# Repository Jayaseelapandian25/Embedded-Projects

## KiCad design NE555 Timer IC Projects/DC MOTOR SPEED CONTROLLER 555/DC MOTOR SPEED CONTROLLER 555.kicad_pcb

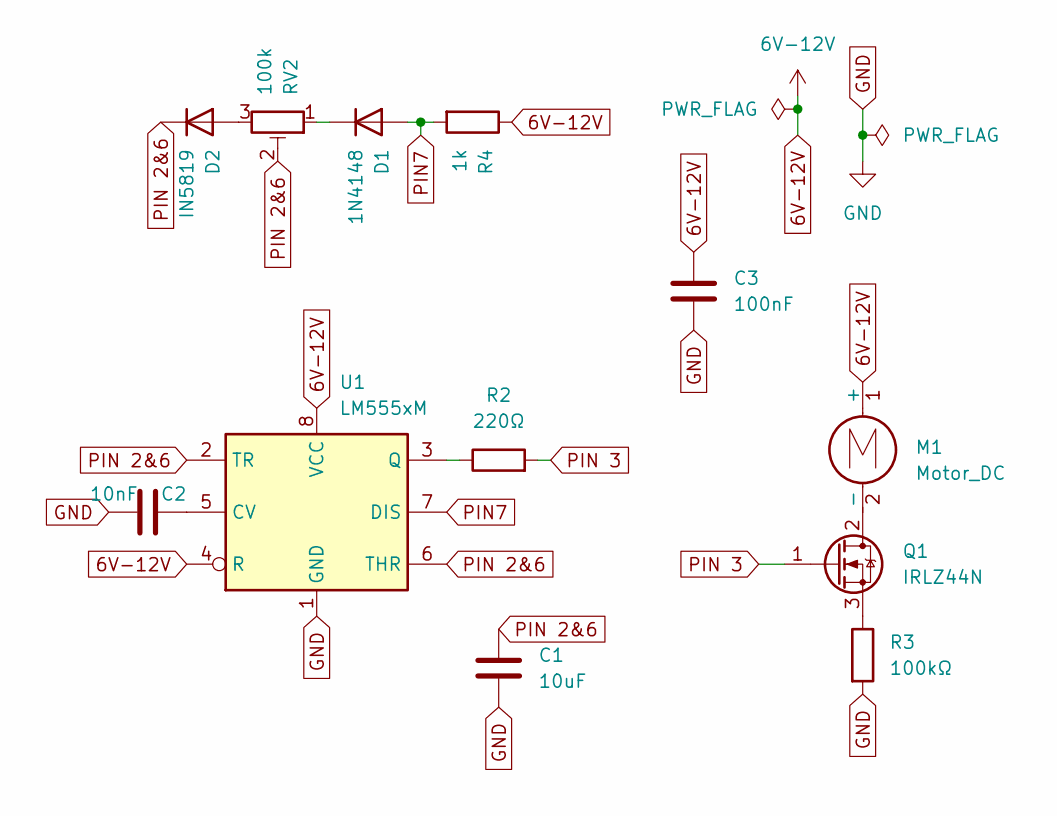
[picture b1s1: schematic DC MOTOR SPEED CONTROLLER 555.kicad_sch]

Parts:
C1: 10uF; C_0805_2012Metric_Pad1.18x1.45mm_HandSolder
C2: 10nF; C_0805_2012Metric_Pad1.18x1.45mm_HandSolder
C3: 100nF; C_0805_2012Metric_Pad1.18x1.45mm_HandSolder
D1: 1N4148; D_SOD-123
D2: IN5819; D_SOD-123
M1: Motor_DC; PinHeader_1x02_P2.54mm_Vertical
Q1: IRLZ44N; TO-220-3_Vertical
R2: 220Ω; R_0805_2012Metric_Pad1.20x1.40mm_HandSolder
R3: 100kΩ; R_0805_2012Metric_Pad1.20x1.40mm_HandSolder
R4: 1k; R_0805_2012Metric_Pad1.20x1.40mm_HandSolder
RV2: 100k; Potentiometer_Bourns_3296W_Vertical
U1: LM555xM; SOIC-8_3.9x4.9mm_P1.27mm

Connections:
6V-12V: C3.1, M1.1 (+), R4.1, U1.4 (R), U1.8 (VCC)
GND: C1.2, C2.1, C3.2, R3.2, U1.1 (GND)
unnamed: D1.1 (K), RV2.1
unnamed: D2.2 (A), RV2.3
unnamed: M1.2 (-), Q1.2 (D)
unnamed: Q1.3 (S), R3.1
unnamed: C2.2, U1.5 (CV)
unnamed: R2.1, U1.3 (Q)
PIN7: D1.2 (A), R4.2, U1.7 (DIS)
PIN 2&6: C1.1, D2.1 (K), RV2.2, U1.2 (TR), U1.6 (THR)
PIN 3: Q1.1 (G), R2.2

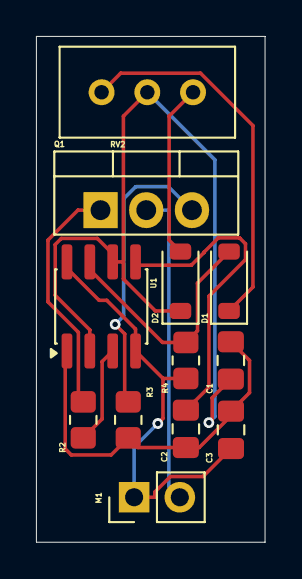
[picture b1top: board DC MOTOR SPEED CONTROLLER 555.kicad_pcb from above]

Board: 2 copper layers, 12.7 x 28.1 mm, 12 parts (0 on the bottom side), 11 nets.

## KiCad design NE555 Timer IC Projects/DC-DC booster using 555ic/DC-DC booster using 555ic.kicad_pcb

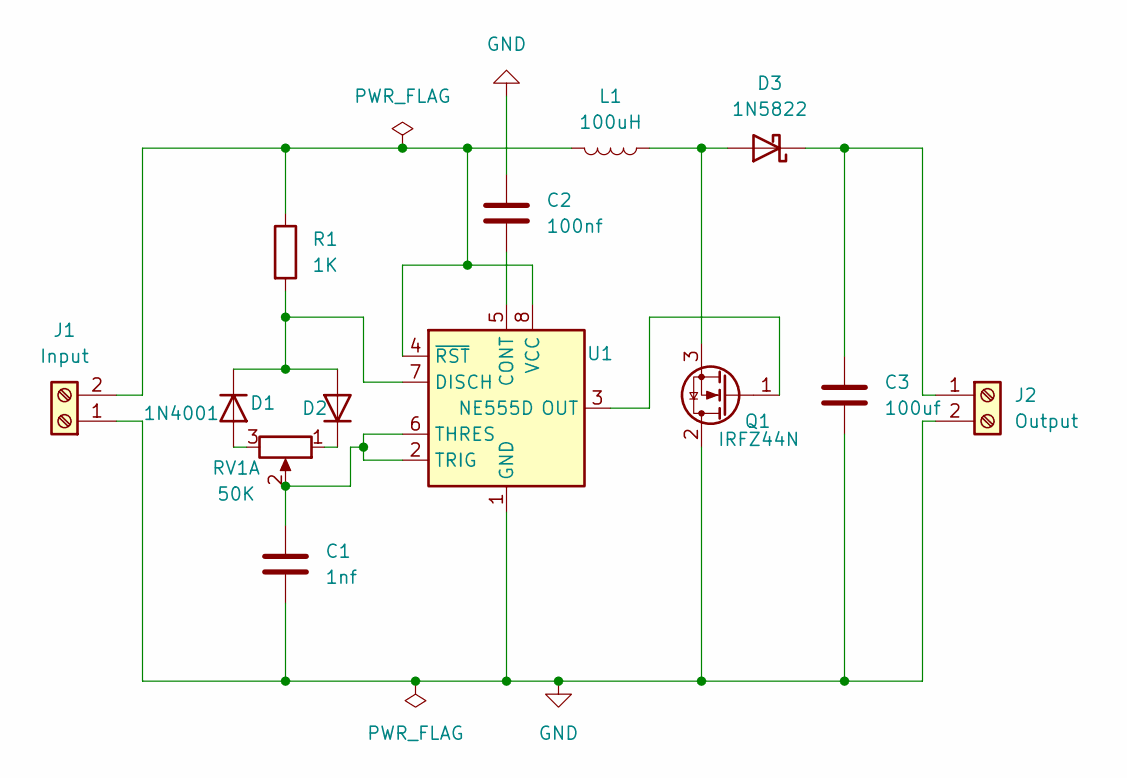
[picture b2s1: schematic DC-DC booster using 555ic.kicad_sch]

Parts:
C1: 1nf; CP_Radial_D6.3mm_P2.50mm
C2: 100nf; C_Disc_D5.0mm_W2.5mm_P5.00mm
C3: 100uf; CP_Radial_D6.3mm_P2.50mm
D1, D2: 1N4001; D_DO-41_SOD81_P10.16mm_Horizontal
D3: 1N5822; D_DO-201AD_P15.24mm_Horizontal
J1: Input; TerminalBlock_MaiXu_MX126-5.0-02P_1x02_P5.00mm
J2: Output; TerminalBlock_MaiXu_MX126-5.0-02P_1x02_P5.00mm
L1: 100uH; L_Radial_D10.0mm_P5.00mm_Fastron_07P
Q1: IRFZ44N; TO-220-3_Vertical
R1: 1K; R_Axial_DIN0207_L6.3mm_D2.5mm_P7.62mm_Horizontal
RV1: 50K; Potentiometer_Bourns_3296W_Vertical
U1: NE555D; SOIC-8_3.9x4.9mm_P1.27mm

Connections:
GND: C1.2, C2.2, C3.2, J1.1, J2.2, Q1.2 (D), U1.1 (GND)
unnamed: D1.2 (A), RV1.3
unnamed: D1.1 (K), D2.2 (A), R1.2, U1.7 (DISCH)
unnamed: D2.1 (K), RV1.1
unnamed: D3.2 (A), L1.1, Q1.3 (S)
unnamed: C3.1, D3.1 (K), J2.1
unnamed: J1.2, L1.2, R1.1, U1.4 (~RST), U1.8 (VCC)
unnamed: Q1.1 (G), U1.3 (OUT)
unnamed: C2.1, U1.5 (CONT)
unnamed: C1.1, RV1.2, U1.2 (TRIG), U1.6 (THRES)

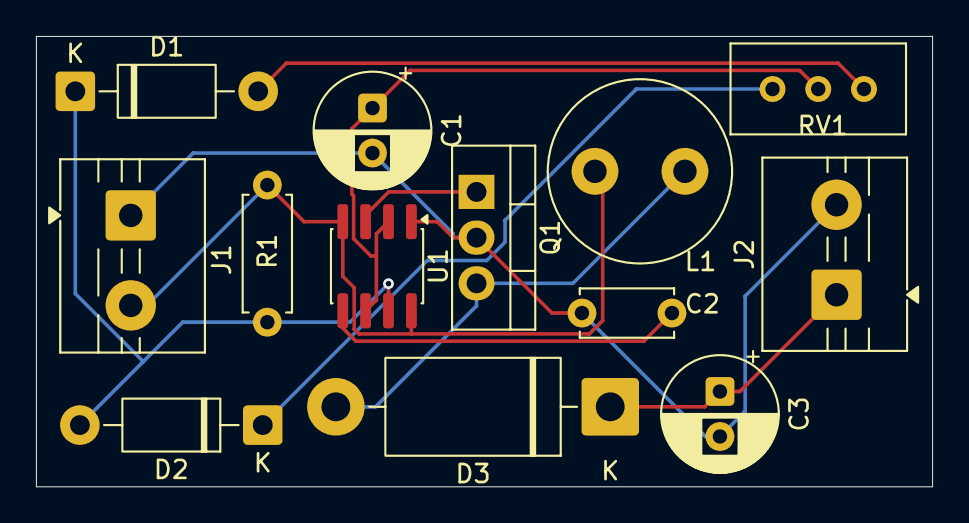
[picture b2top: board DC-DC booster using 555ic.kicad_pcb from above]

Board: 2 copper layers, 49.8 x 25.0 mm, 13 parts (0 on the bottom side), 10 nets.

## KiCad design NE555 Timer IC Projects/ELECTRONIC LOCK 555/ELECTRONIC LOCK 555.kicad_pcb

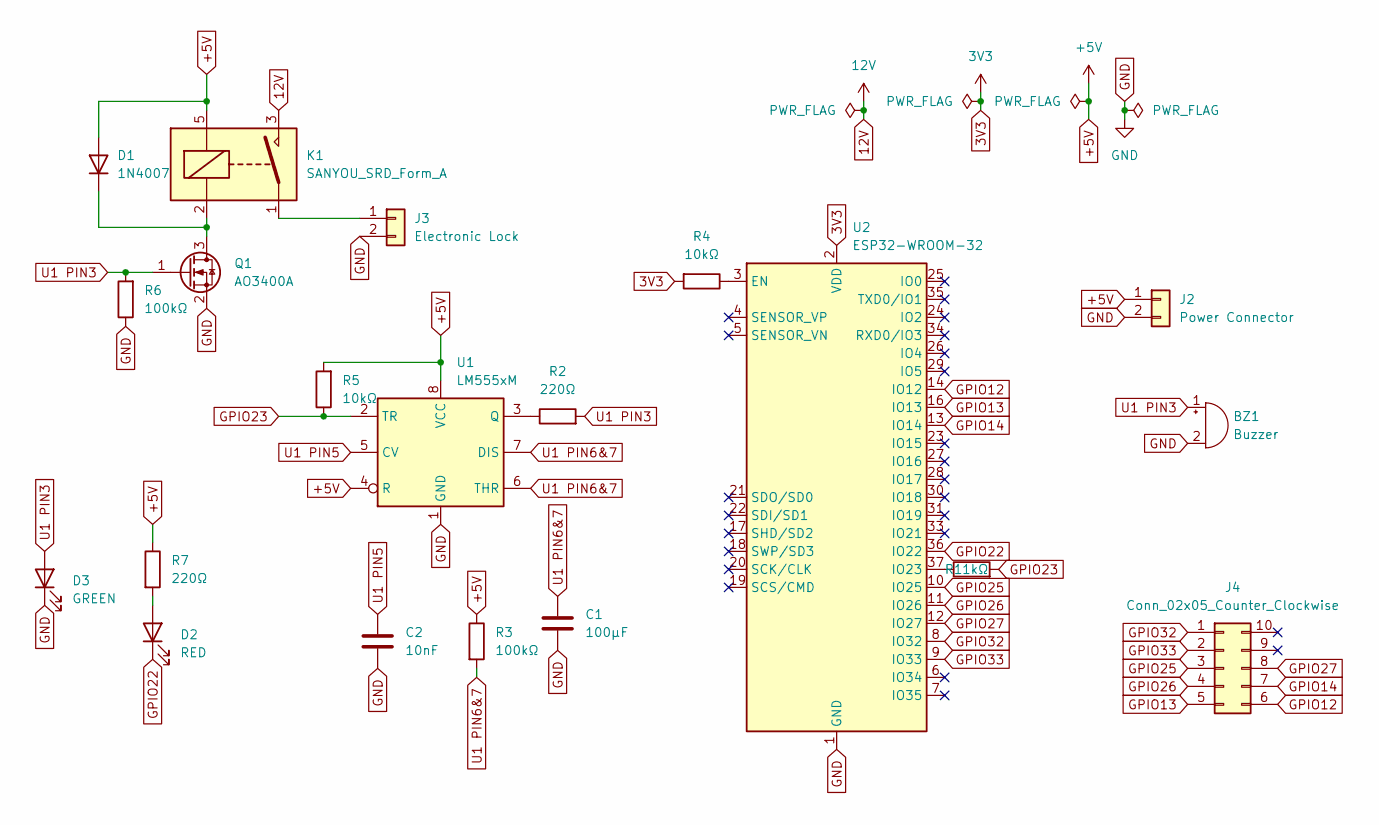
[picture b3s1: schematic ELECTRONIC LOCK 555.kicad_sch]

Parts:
BZ1: Buzzer; Buzzer_TDK_PS1240P02BT_D12.2mm_H6.5mm
C1: 100µF; C_0805_2012Metric
C2: 10nF; C_0805_2012Metric
D1: 1N4007; D_SMA
D2: RED; LED_0805_2012Metric
D3: GREEN; LED_0805_2012Metric
J2: Power Connector; JST_PH_B2B-PH-K_1x02_P2.00mm_Vertical
J3: Electronic Lock; JST_PH_B2B-PH-K_1x02_P2.00mm_Vertical
J4: Conn_02x05_Counter_Clockwise; IDC-Header_2x05_P2.54mm_Horizontal
K1: SANYOU_SRD_Form_A; Relay_SPST_SANYOU_SRD_Series_Form_A
Q1: AO3400A; SOT-23
R1: 1kΩ; R_0805_2012Metric
R2, R7: 220Ω; R_0805_2012Metric
R3, R6: 100kΩ; R_0805_2012Metric
R4, R5: 10kΩ; R_0805_2012Metric
U1: LM555xM; SOIC-8_3.9x4.9mm_P1.27mm
U2: ESP32-WROOM-32

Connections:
3V3: R4.2, U2.2 (VDD)
12V: K1.3
+5V: D1.2 (A), J2.1, K1.5, R3.1, R5.2, R7.1, U1.4 (R), U1.8 (VCC)
GND: BZ1.2 (-), C1.2, C2.2, D3.1 (K), J2.2, J3.2, Q1.2 (S), R6.1, U1.1 (GND), U2.1 (GND), U2.15 (GND), U2.38 (GND), U2.39 (GND)
GPIO12: J4.6, U2.14 (IO12)
GPIO13: J4.5, U2.16 (IO13)
GPIO14: J4.7, U2.13 (IO14)
GPIO22: D2.1 (K), U2.36 (IO22)
GPIO23: R1.2, R5.1, U1.2 (TR)
GPIO25: J4.3, U2.10 (IO25)
GPIO26: J4.4, U2.11 (IO26)
GPIO27: J4.8, U2.12 (IO27)
GPIO32: J4.1, U2.8 (IO32)
GPIO33: J4.2, U2.9 (IO33)
unnamed: D1.1 (K), K1.2, Q1.3 (D)
unnamed: D2.2 (A), R7.2
unnamed: J3.1, K1.1
unnamed: R2.1, U1.3 (Q)
unnamed: R4.1, U2.3 (EN)
unnamed: R1.1, U2.37 (IO23)
U1 PIN3: BZ1.1 (+), D3.2 (A), Q1.1 (G), R2.2, R6.2
U1 PIN5: C2.1, U1.5 (CV)
U1 PIN6&7: C1.1, R3.2, U1.6 (THR), U1.7 (DIS)

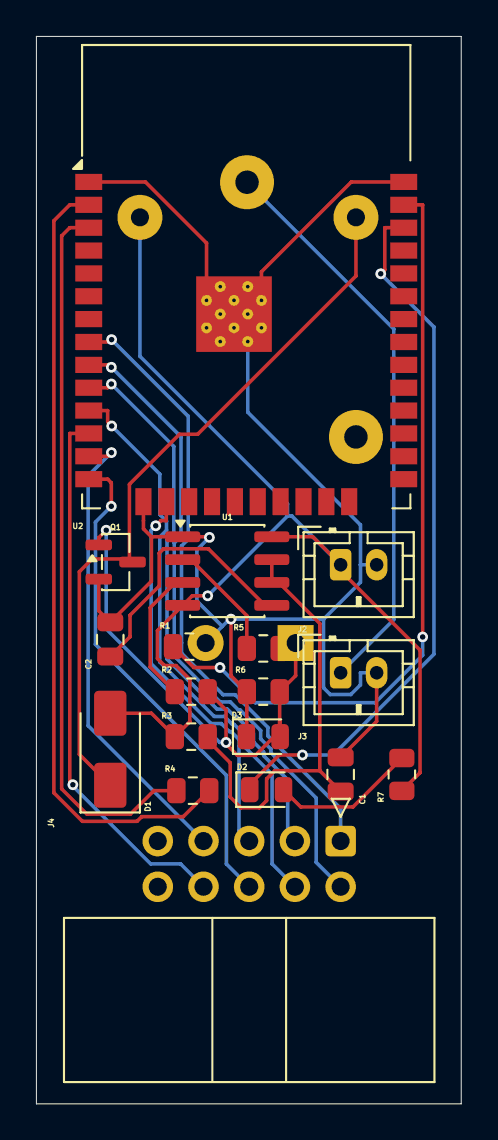
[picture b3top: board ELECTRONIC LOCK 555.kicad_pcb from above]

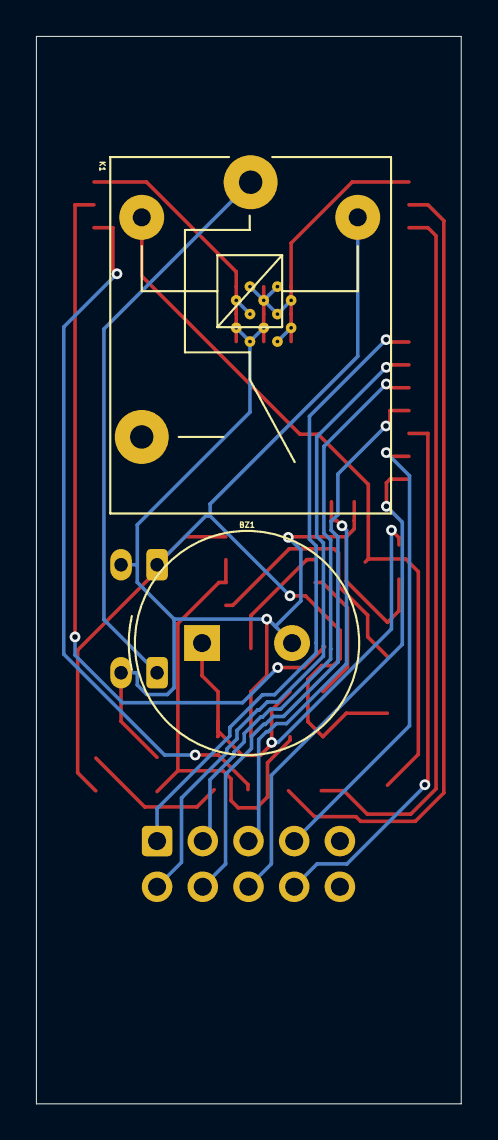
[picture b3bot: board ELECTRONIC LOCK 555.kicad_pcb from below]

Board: 2 copper layers, 23.6 x 59.3 mm, 20 parts (2 on the bottom side), 22 nets.

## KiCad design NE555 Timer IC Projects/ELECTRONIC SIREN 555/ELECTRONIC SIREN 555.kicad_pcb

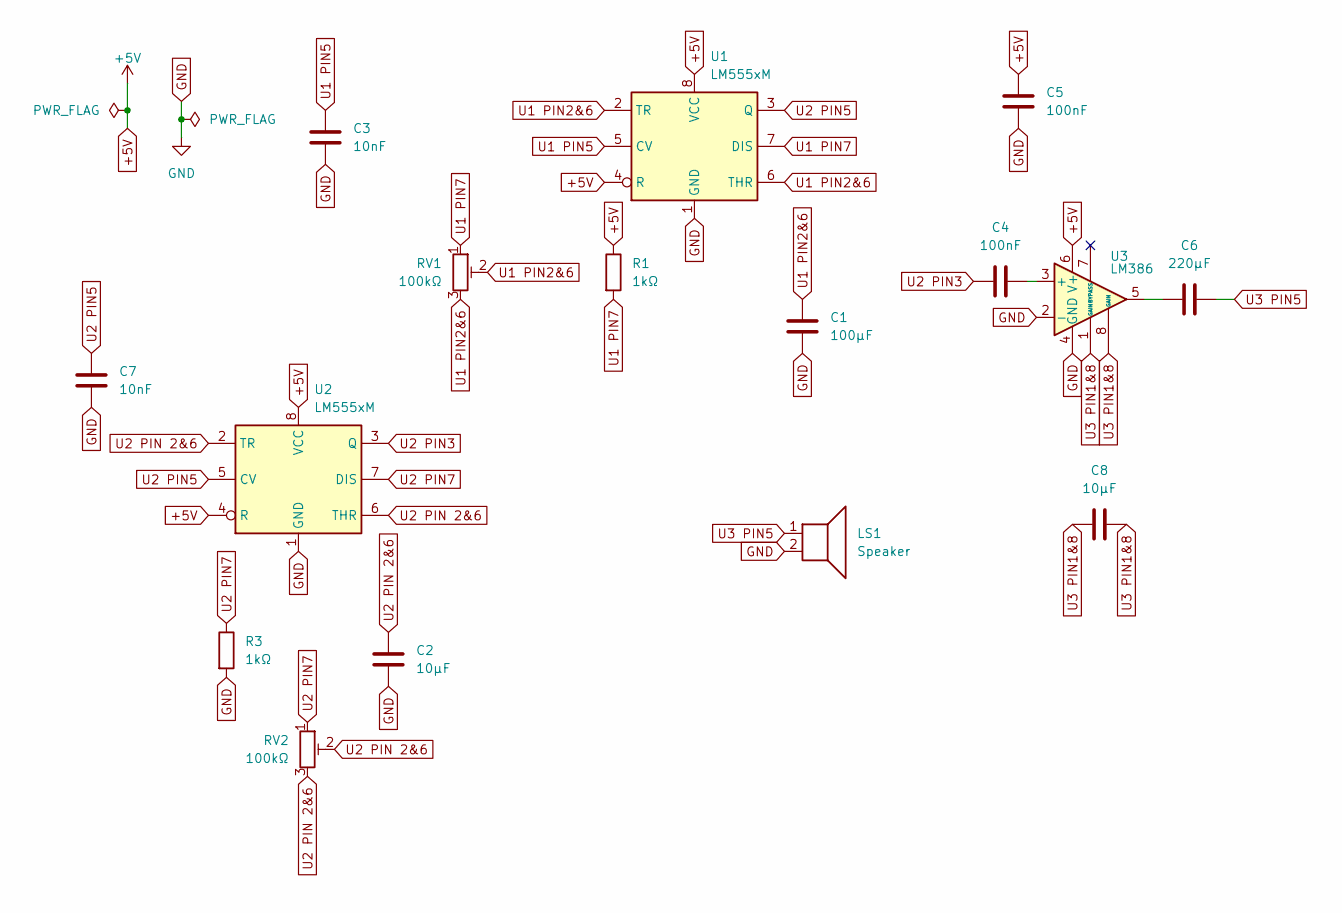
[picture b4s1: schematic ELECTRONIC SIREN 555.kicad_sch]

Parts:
C1: 100µF; C_0805_2012Metric
C2, C8: 10µF; C_0805_2012Metric
C3, C7: 10nF; C_0805_2012Metric
C4, C5: 100nF; C_0805_2012Metric
C6: 220µF; CP_Elec_6.3x5.4
LS1: Speaker; JST_PH_B2B-PH-K_1x02_P2.00mm_Vertical
R1, R3: 1kΩ; R_0805_2012Metric
RV1, RV2: 100kΩ; Potentiometer_Bourns_3296W_Vertical
U1, U2: LM555xM; SOIC-8_3.9x4.9mm_P1.27mm
U3: LM386; SOIC-8_3.9x4.9mm_P1.27mm

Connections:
+5V: C5.1, R1.1, U1.4 (R), U1.8 (VCC), U2.4 (R), U2.8 (VCC), U3.6 (V+)
GND: C1.2, C2.2, C3.2, C5.2, C7.2, LS1.2, R3.2, U1.1 (GND), U2.1 (GND), U3.2 (-), U3.4 (GND)
unnamed: C6.1, U3.5
unnamed: C4.2, U3.3 (+)
U1 PIN2&6: C1.1, RV1.2, RV1.3, U1.2 (TR), U1.6 (THR)
U1 PIN5: C3.1, U1.5 (CV)
U1 PIN7: R1.2, RV1.1, U1.7 (DIS)
U2 PIN3: C4.1, U2.3 (Q)
U2 PIN5: C7.1, U1.3 (Q), U2.5 (CV)
U2 PIN7: R3.1, RV2.1, U2.7 (DIS)
U2 PIN 2&6: C2.1, RV2.2, RV2.3, U2.2 (TR), U2.6 (THR)
U3 PIN1&8: C8.1, C8.2, U3.1 (GAIN), U3.8 (GAIN)
U3 PIN5: C6.2, LS1.1

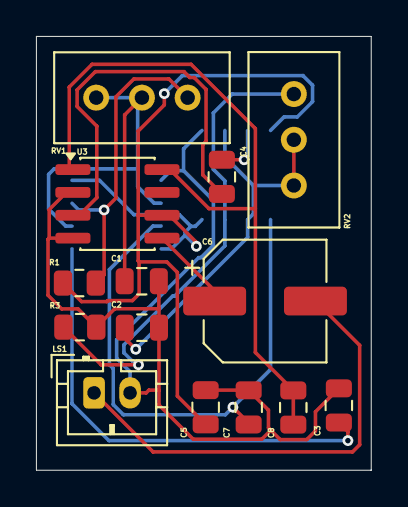
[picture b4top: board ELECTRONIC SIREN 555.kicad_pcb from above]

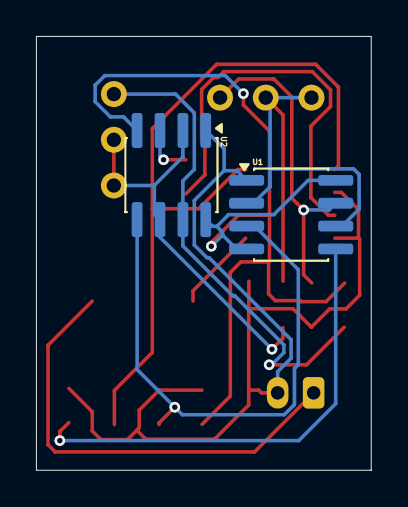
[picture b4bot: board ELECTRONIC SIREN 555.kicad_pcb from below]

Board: 2 copper layers, 18.6 x 24.1 mm, 16 parts (2 on the bottom side), 13 nets.

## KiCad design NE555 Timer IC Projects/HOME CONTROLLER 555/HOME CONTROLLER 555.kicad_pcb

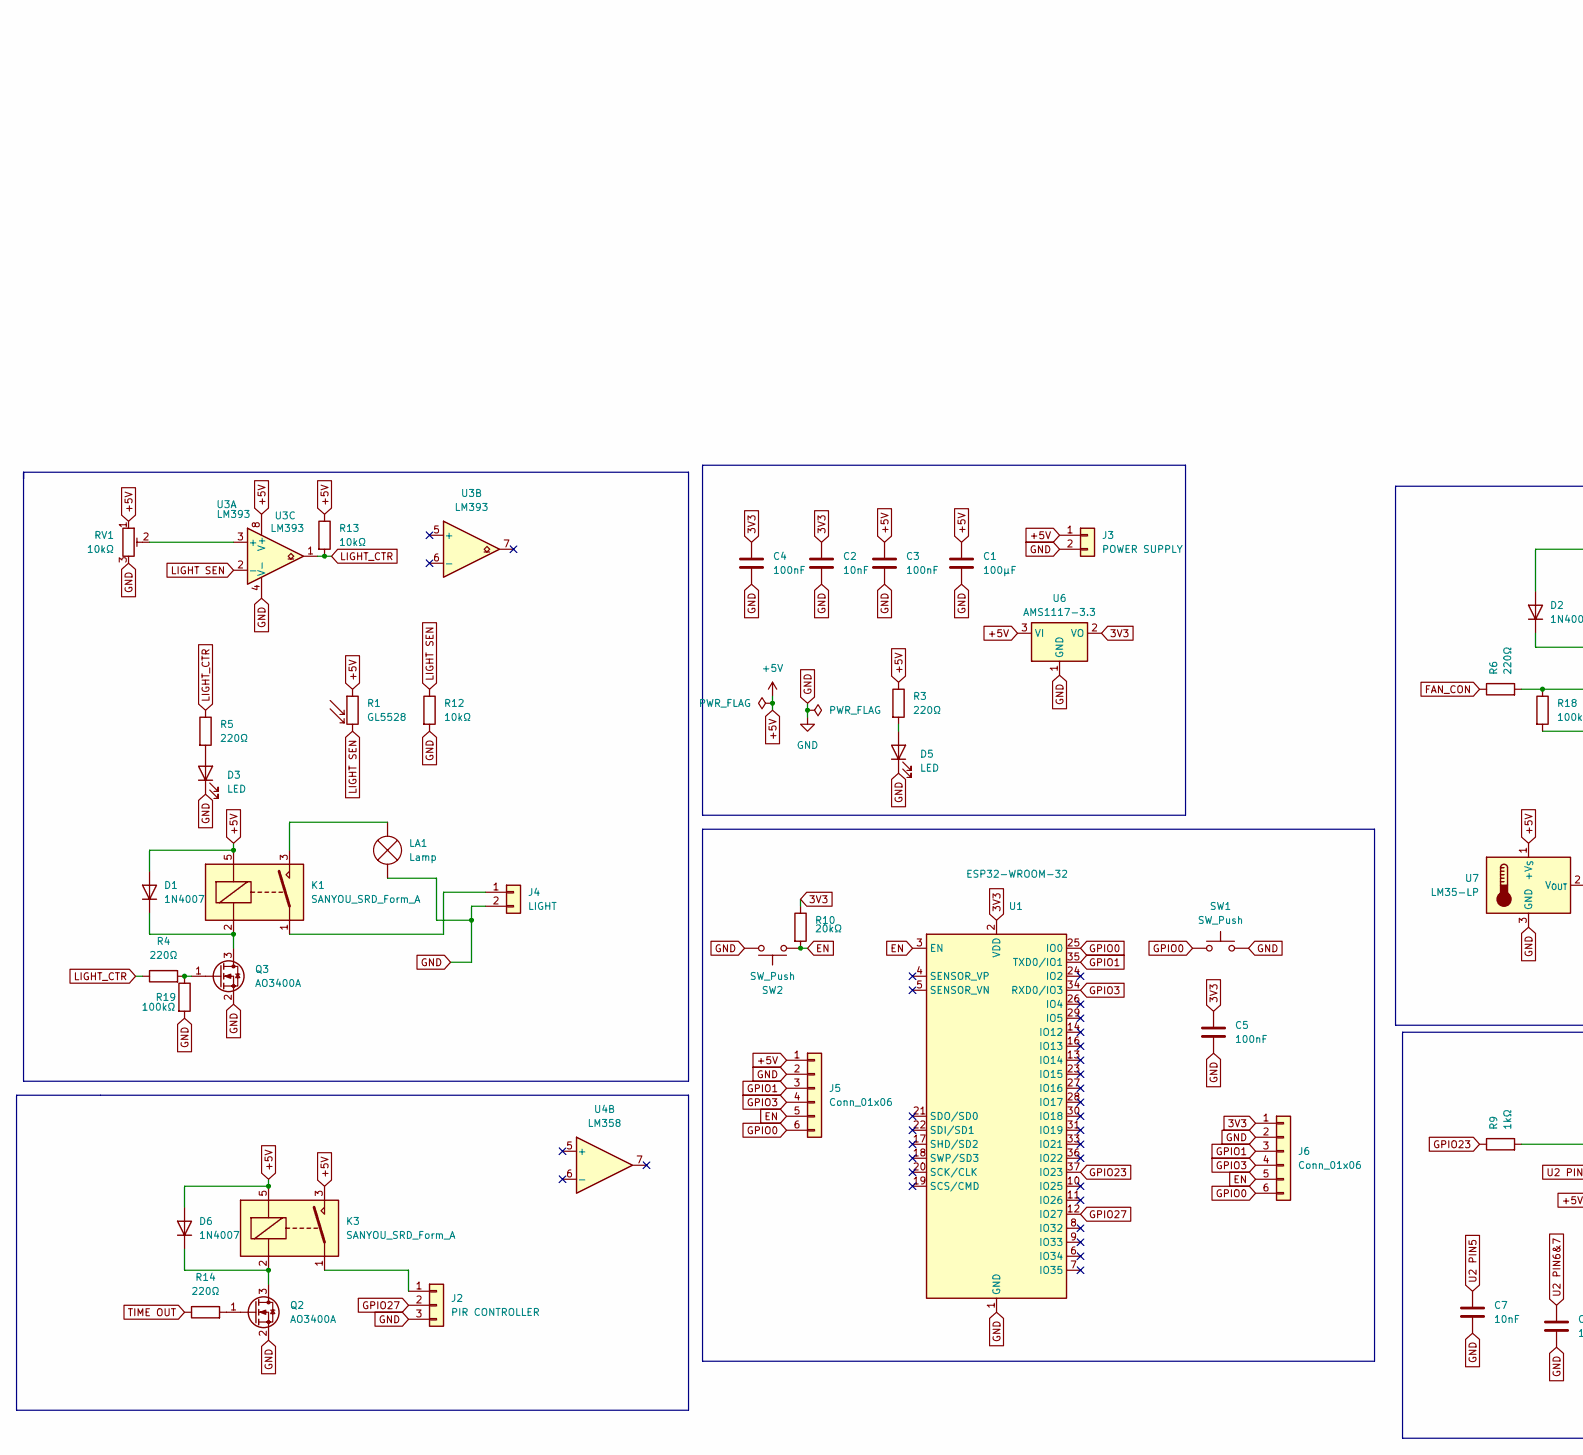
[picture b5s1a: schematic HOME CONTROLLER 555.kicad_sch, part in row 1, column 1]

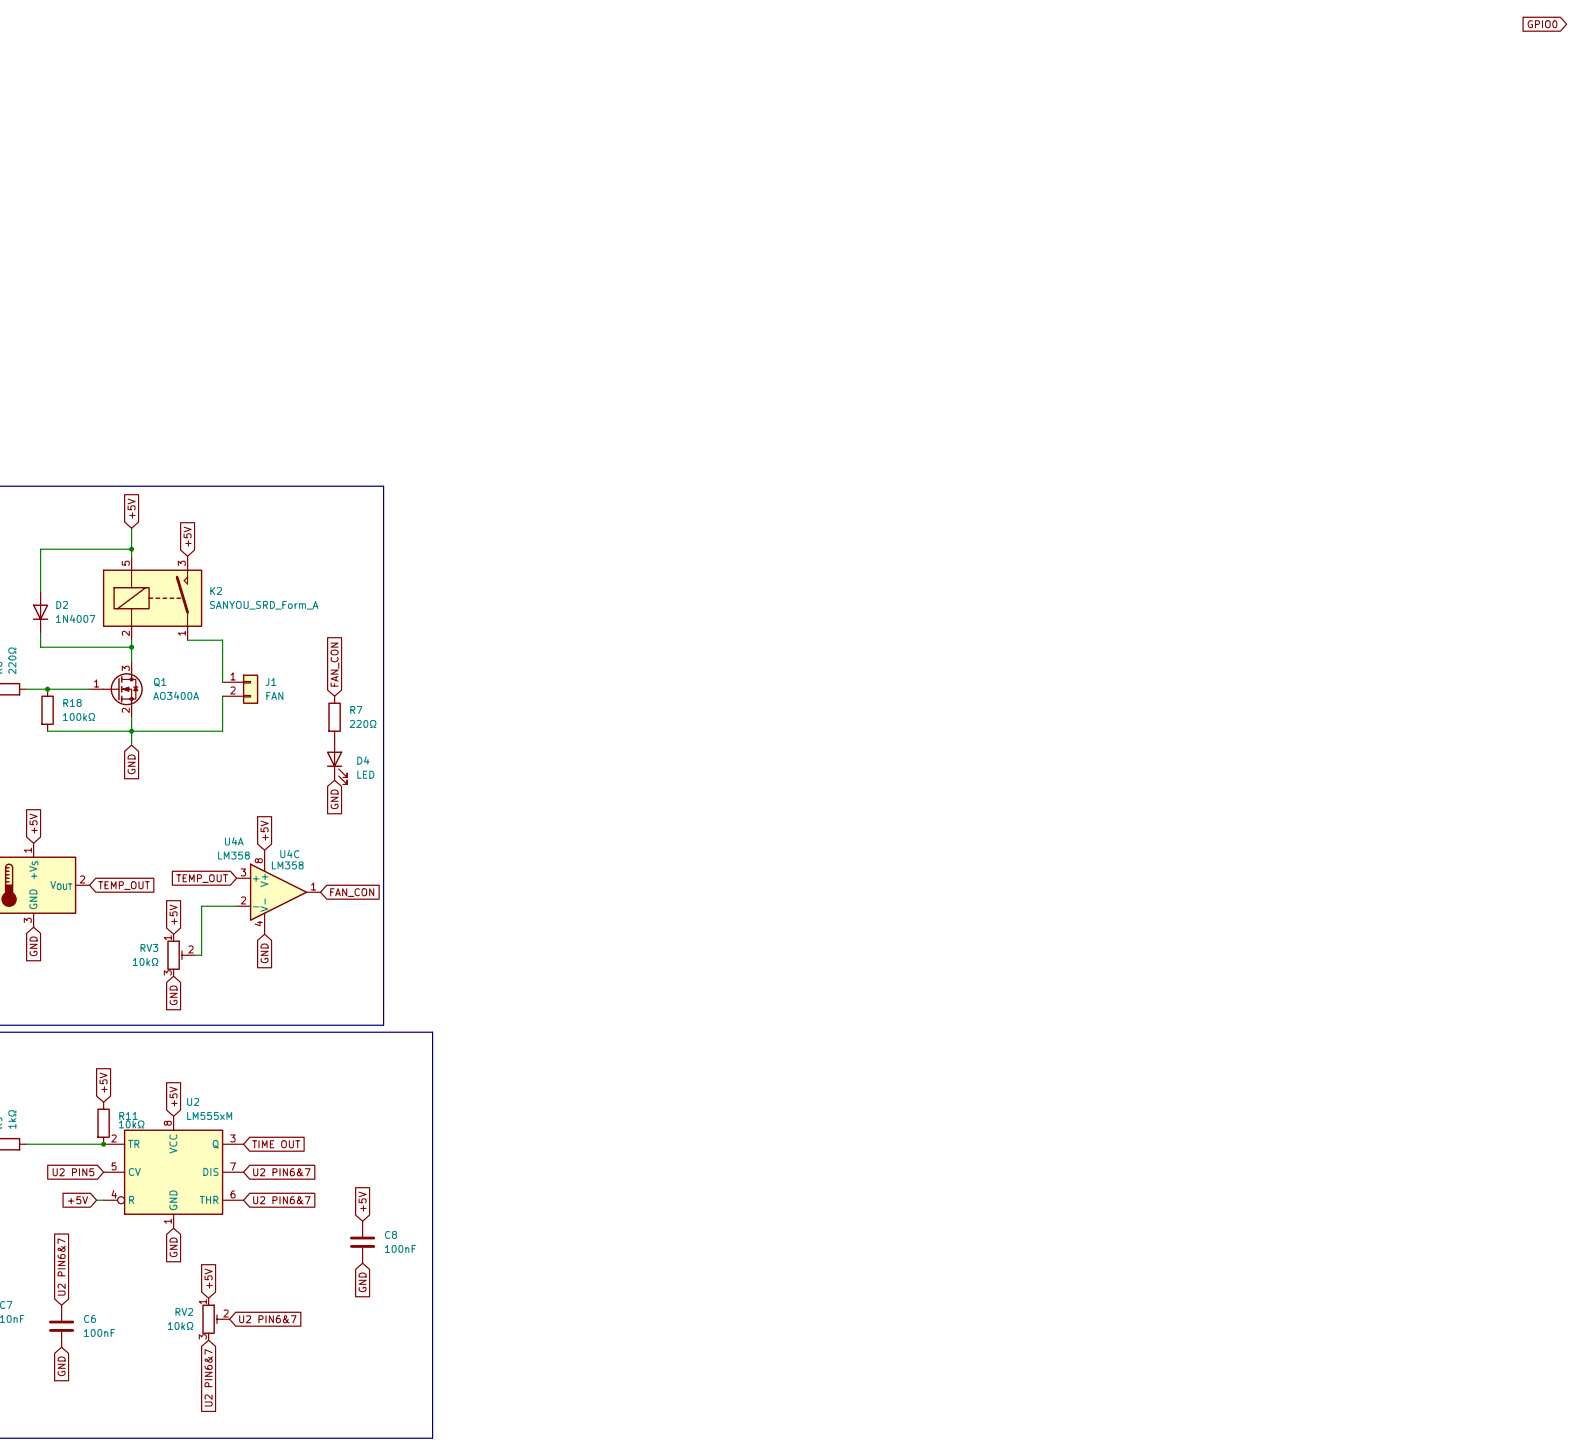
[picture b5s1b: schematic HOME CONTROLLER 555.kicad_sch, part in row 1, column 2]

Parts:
C1: 100µF; C_0805_2012Metric
C2, C7: 10nF; C_0805_2012Metric
C3, C4, C5, C6, C8: 100nF; C_0805_2012Metric
D1, D2, D6: 1N4007; D_SMA
D3, D4, D5: LED; LED_0805_2012Metric
J1: FAN; JST_PH_B2B-PH-K_1x02_P2.00mm_Vertical
J2: PIR CONTROLLER; PinHeader_1x03_P2.54mm_Vertical
J3: POWER SUPPLY; JST_PH_B2B-PH-K_1x02_P2.00mm_Vertical
J4: LIGHT; JST_PH_B2B-PH-K_1x02_P2.00mm_Vertical
J5, J6: Conn_01x06; PinHeader_1x06_P2.54mm_Vertical
K1, K2, K3: SANYOU_SRD_Form_A; Relay_SPST_SANYOU_SRD_Series_Form_A
LA1: Lamp; JST_PH_B2B-PH-K_1x02_P2.00mm_Vertical
Q1, Q2, Q3: AO3400A; SOT-23
R1: GL5528; R_LDR_5.1x4.3mm_P3.4mm_Vertical
R3, R4, R5, R6, R7, R14: 220Ω; R_0805_2012Metric
R9: 1kΩ; R_0805_2012Metric
R10: 20kΩ; R_0805_2012Metric
R11, R12, R13: 10kΩ; R_0805_2012Metric
R18, R19: 100kΩ; R_0805_2012Metric
RV1, RV2, RV3: 10kΩ; Potentiometer_Bourns_3296W_Vertical
SW1, SW2: SW_Push; SW_SPST_TL3342
U1: ESP32-WROOM-32
U2: LM555xM; SOIC-8_3.9x4.9mm_P1.27mm
U3: LM393; SOIC-8_3.9x4.9mm_P1.27mm
U4: LM358; SOIC-8_3.9x4.9mm_P1.27mm
U6: AMS1117-3.3; SOT-223-3_TabPin2
U7: LM35-LP; TO-92_Inline

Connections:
3V3: C2.1, C4.1, C5.1, J6.1, R10.1, U1.2 (VDD), U6.2 (VO)
+5V: C1.1, C3.1, C8.1, D1.2 (A), D2.2 (A), D6.2 (A), J3.1, J5.1, K1.5, K2.3, K2.5, K3.3, K3.5, R1.1, R3.1, R11.1, R13.1, RV1.1, RV2.1, RV3.1, U2.4 (R), U2.8 (VCC), U3.8 (V+), U4.8 (V+), U6.3 (VI), U7.1 (+V_{S})
EN: J5.5, J6.5, R10.2, SW2.1, U1.3 (EN)
FAN_CON: R6.1, R7.1, U4.1
GND: C1.2, C2.2, C3.2, C4.2, C5.2, C6.2, C7.2, C8.2, D3.1 (K), D4.1 (K), D5.1 (K), J1.2, J2.3, J3.2, J4.2, J5.2, J6.2, LA1.1 (-), Q1.2 (S), Q2.2 (S), Q3.2 (S), R12.2, R18.2, R19.2, RV1.3, RV3.3, SW1.2, SW2.2, U1.1 (GND), U1.15 (GND), U1.38 (GND), U1.39 (GND), U2.1 (GND), U3.4 (V-), U4.4 (V-), U6.1 (GND), U7.3 (GND)
GPIO0: J5.6, J6.6, SW1.1, U1.25 (IO0)
GPIO1: J5.3, J6.3, U1.35 (TXD0/IO1)
GPIO3: J5.4, J6.4, U1.34 (RXD0/IO3)
GPIO23: R9.1, U1.37 (IO23)
GPIO27: J2.2, U1.12 (IO27)
LIGHT SEN: R1.2, R12.1, U3.2 (-)
LIGHT_CTR: R4.1, R5.1, R13.2, U3.1
unnamed: D1.1 (K), K1.2, Q3.3 (D)
unnamed: D2.1 (K), K2.2, Q1.3 (D)
unnamed: D3.2 (A), R5.2
unnamed: D4.2 (A), R7.2
unnamed: D5.2 (A), R3.2
unnamed: D6.1 (K), K3.2, Q2.3 (D)
unnamed: J1.1, K2.1
unnamed: J2.1, K3.1
unnamed: J4.1, K1.1
unnamed: K1.3, LA1.2 (+)
unnamed: Q1.1 (G), R6.2, R18.1
unnamed: Q2.1 (G), R14.2
unnamed: Q3.1 (G), R4.2, R19.1
unnamed: R9.2, R11.2, U2.2 (TR)
unnamed: RV1.2, U3.3 (+)
unnamed: RV3.2, U4.2 (-)
TEMP_OUT: U4.3 (+), U7.2 (V_{OUT})
TIME OUT: R14.1, U2.3 (Q)
U2 PIN5: C7.1, U2.5 (CV)
U2 PIN6&7: C6.1, RV2.2, RV2.3, U2.6 (THR), U2.7 (DIS)

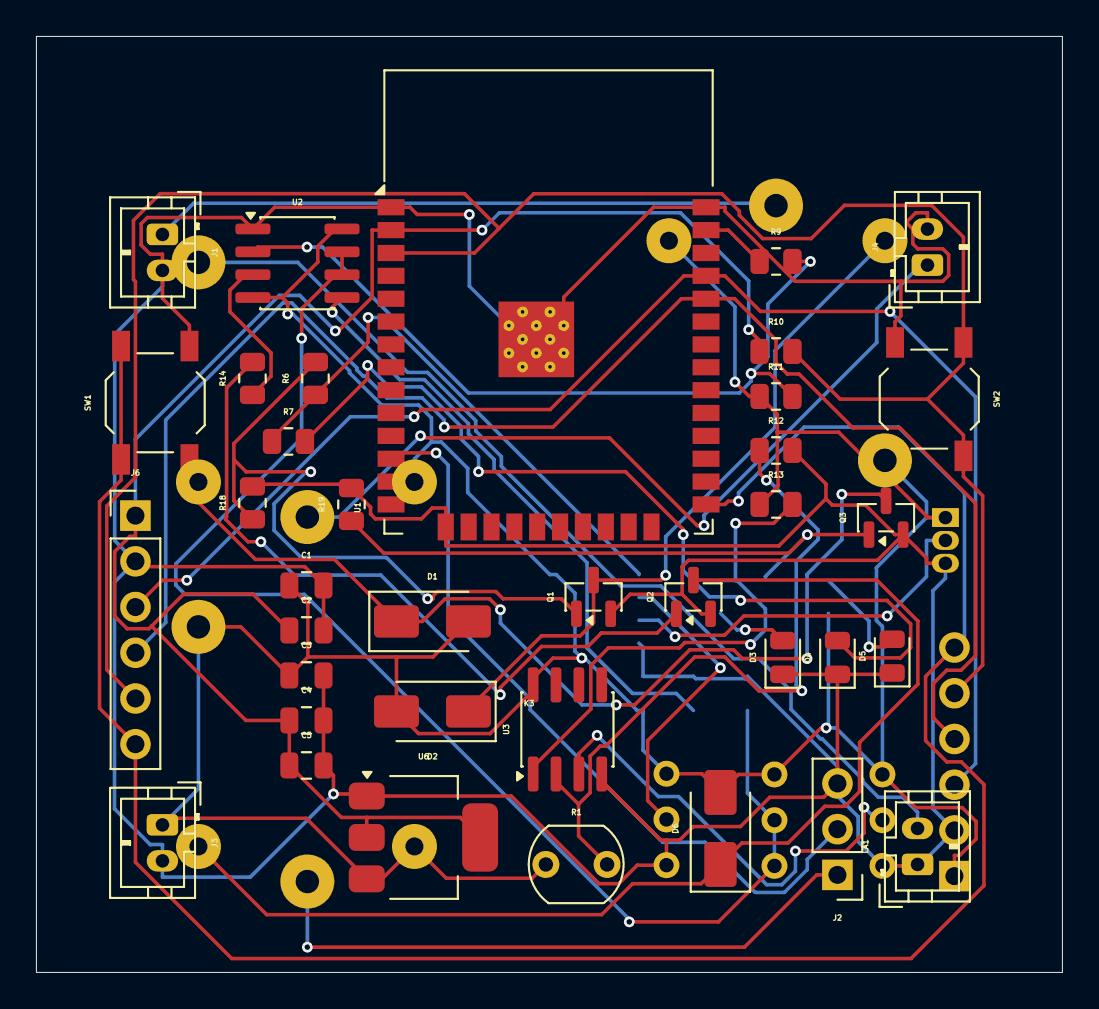
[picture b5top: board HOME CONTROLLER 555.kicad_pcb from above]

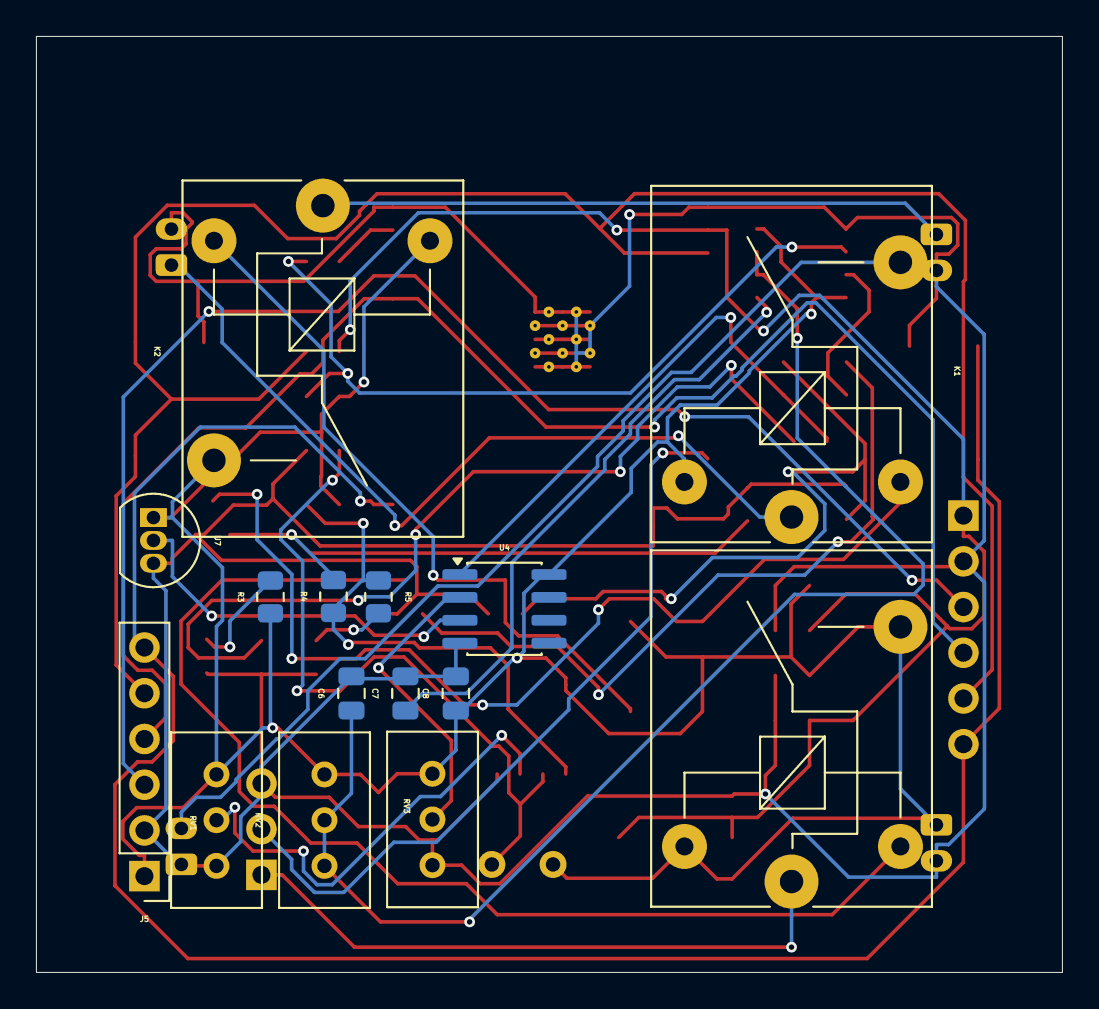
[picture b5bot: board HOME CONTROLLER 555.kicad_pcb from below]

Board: 2 copper layers, 57.0 x 52.0 mm, 52 parts (15 on the bottom side), 32 nets.

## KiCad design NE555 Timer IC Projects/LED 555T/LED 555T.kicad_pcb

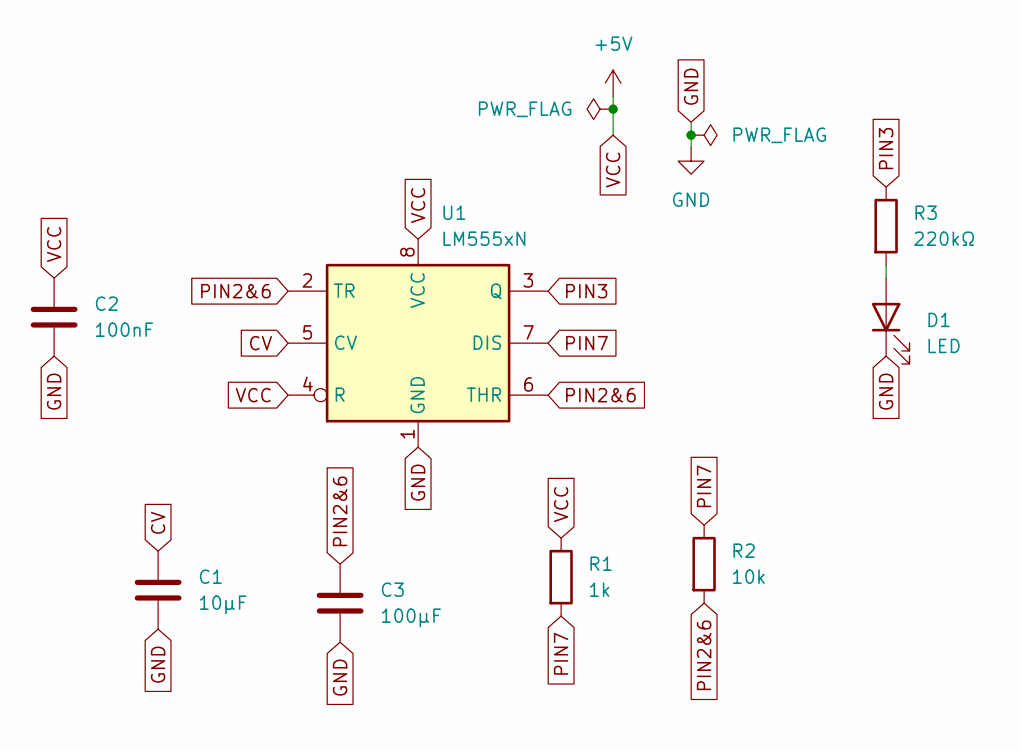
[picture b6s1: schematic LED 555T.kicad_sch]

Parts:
C1: 10µF; C_0805_2012Metric_Pad1.18x1.45mm_HandSolder
C2: 100nF; C_0805_2012Metric_Pad1.18x1.45mm_HandSolder
C3: 100µF; C_0805_2012Metric_Pad1.18x1.45mm_HandSolder
D1: LED; LED_0805_2012Metric
R1: 1k; R_0805_2012Metric_Pad1.20x1.40mm_HandSolder
R2: 10k; R_0805_2012Metric_Pad1.20x1.40mm_HandSolder
R3: 220kΩ; R_0805_2012Metric_Pad1.20x1.40mm_HandSolder
U1: LM555xN; DIP-8_W7.62mm

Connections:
CV: C1.1, U1.5 (CV)
GND: C1.2, C2.2, C3.2, D1.1 (K), U1.1 (GND)
unnamed: D1.2 (A), R3.2
PIN2&6: C3.1, R2.2, U1.2 (TR), U1.6 (THR)
PIN3: R3.1, U1.3 (Q)
PIN7: R1.2, R2.1, U1.7 (DIS)
VCC: C2.1, R1.1, U1.4 (R), U1.8 (VCC)

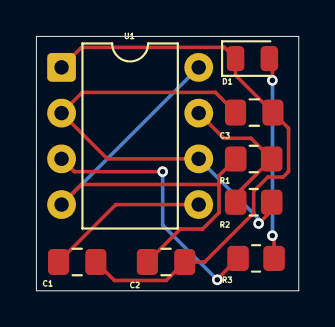
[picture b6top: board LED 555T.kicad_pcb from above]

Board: 2 copper layers, 14.6 x 14.1 mm, 8 parts (0 on the bottom side), 7 nets.

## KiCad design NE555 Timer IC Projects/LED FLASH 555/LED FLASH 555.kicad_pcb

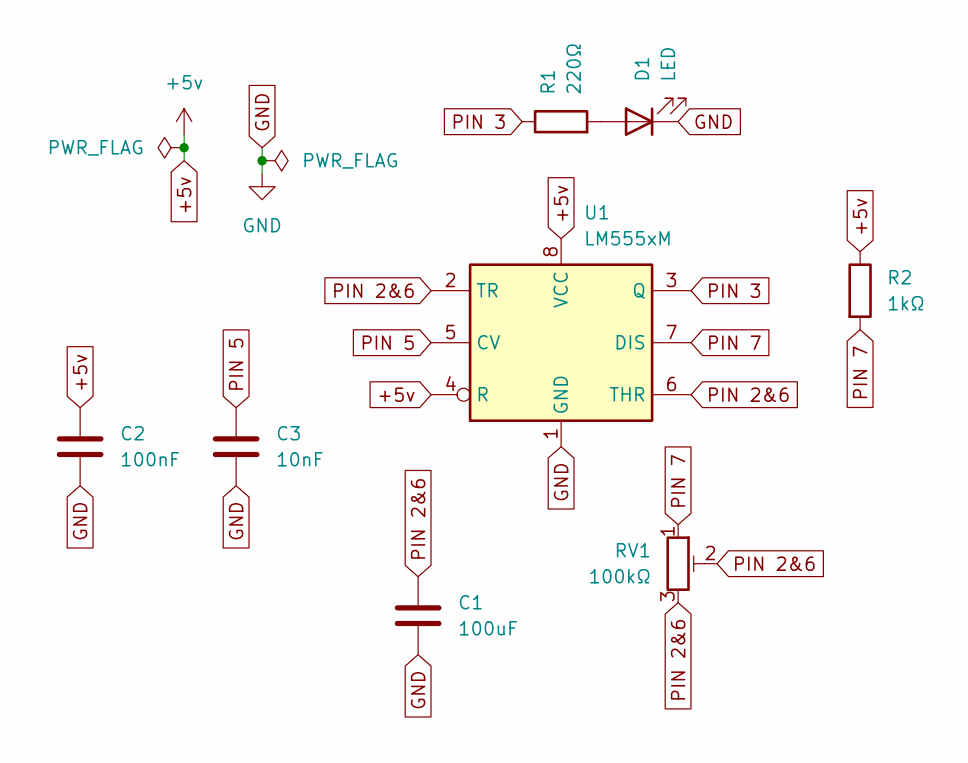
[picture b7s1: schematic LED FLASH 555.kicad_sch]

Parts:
C1: 100uF; C_0805_2012Metric_Pad1.18x1.45mm_HandSolder
C2: 100nF; C_0805_2012Metric_Pad1.18x1.45mm_HandSolder
C3: 10nF; C_0805_2012Metric_Pad1.18x1.45mm_HandSolder
D1: LED; LED_0805_2012Metric_Pad1.15x1.40mm_HandSolder
R1: 220Ω; R_0805_2012Metric_Pad1.20x1.40mm_HandSolder
R2: 1kΩ; R_0805_2012Metric_Pad1.20x1.40mm_HandSolder
RV1: 100kΩ; Potentiometer_Bourns_3296W_Vertical
U1: LM555xM; SOIC-8_3.9x4.9mm_P1.27mm

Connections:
+5v: C2.1, R2.1, U1.4 (R), U1.8 (VCC)
GND: C1.2, C2.2, C3.2, D1.1 (K), U1.1 (GND)
unnamed: D1.2 (A), R1.2
PIN 2&6: C1.1, RV1.2, RV1.3, U1.2 (TR), U1.6 (THR)
PIN 3: R1.1, U1.3 (Q)
PIN 5: C3.1, U1.5 (CV)
PIN 7: R2.2, RV1.1, U1.7 (DIS)

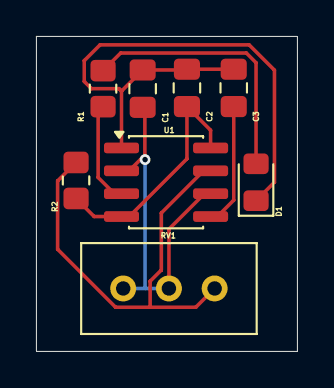
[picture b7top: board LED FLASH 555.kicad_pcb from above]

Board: 2 copper layers, 14.5 x 17.5 mm, 8 parts (0 on the bottom side), 7 nets.

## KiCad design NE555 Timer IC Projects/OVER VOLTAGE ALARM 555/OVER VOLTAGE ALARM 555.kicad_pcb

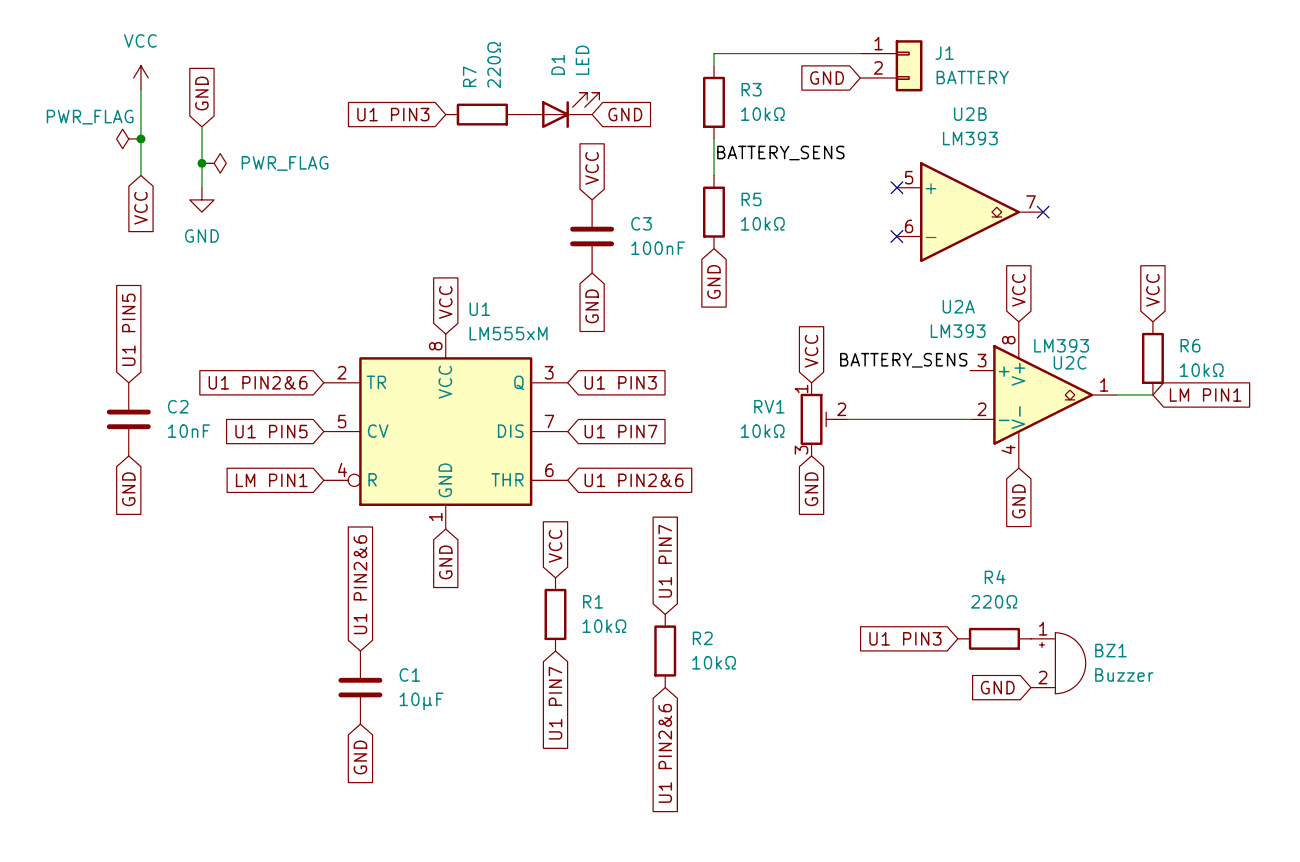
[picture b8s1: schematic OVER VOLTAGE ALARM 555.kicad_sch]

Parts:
BZ1: Buzzer; Buzzer_12x9.5RM7.6
C1: 10µF; C_0805_2012Metric
C2: 10nF; C_0805_2012Metric
C3: 100nF; C_0805_2012Metric
D1: LED; LED_0805_2012Metric_Pad1.15x1.40mm_HandSolder
J1: BATTERY; JST_PH_B2B-PH-K_1x02_P2.00mm_Vertical
R1, R2, R3, R5, R6: 10kΩ; R_0805_2012Metric
R4, R7: 220Ω; R_0805_2012Metric
RV1: 10kΩ; Potentiometer_Bourns_3296W_Vertical
U1: LM555xM; SOIC-8_3.9x4.9mm_P1.27mm
U2: LM393; SOIC-8_3.9x4.9mm_P1.27mm

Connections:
/BATTERY_SENS: R3.2, R5.1, U2.3 (+)
GND: BZ1.2 (-), C1.2, C2.2, C3.2, D1.1 (K), J1.2, R5.2, RV1.3, U1.1 (GND), U2.4 (V-)
LM PIN1: R6.2, U1.4 (R), U2.1
unnamed: BZ1.1 (+), R4.2
unnamed: D1.2 (A), R7.2
unnamed: J1.1, R3.1
unnamed: RV1.2, U2.2 (-)
U1 PIN2&6: C1.1, R2.2, U1.2 (TR), U1.6 (THR)
U1 PIN3: R4.1, R7.1, U1.3 (Q)
U1 PIN5: C2.1, U1.5 (CV)
U1 PIN7: R1.2, R2.1, U1.7 (DIS)
VCC: C3.1, R1.1, R6.1, RV1.1, U1.8 (VCC), U2.8 (V+)
